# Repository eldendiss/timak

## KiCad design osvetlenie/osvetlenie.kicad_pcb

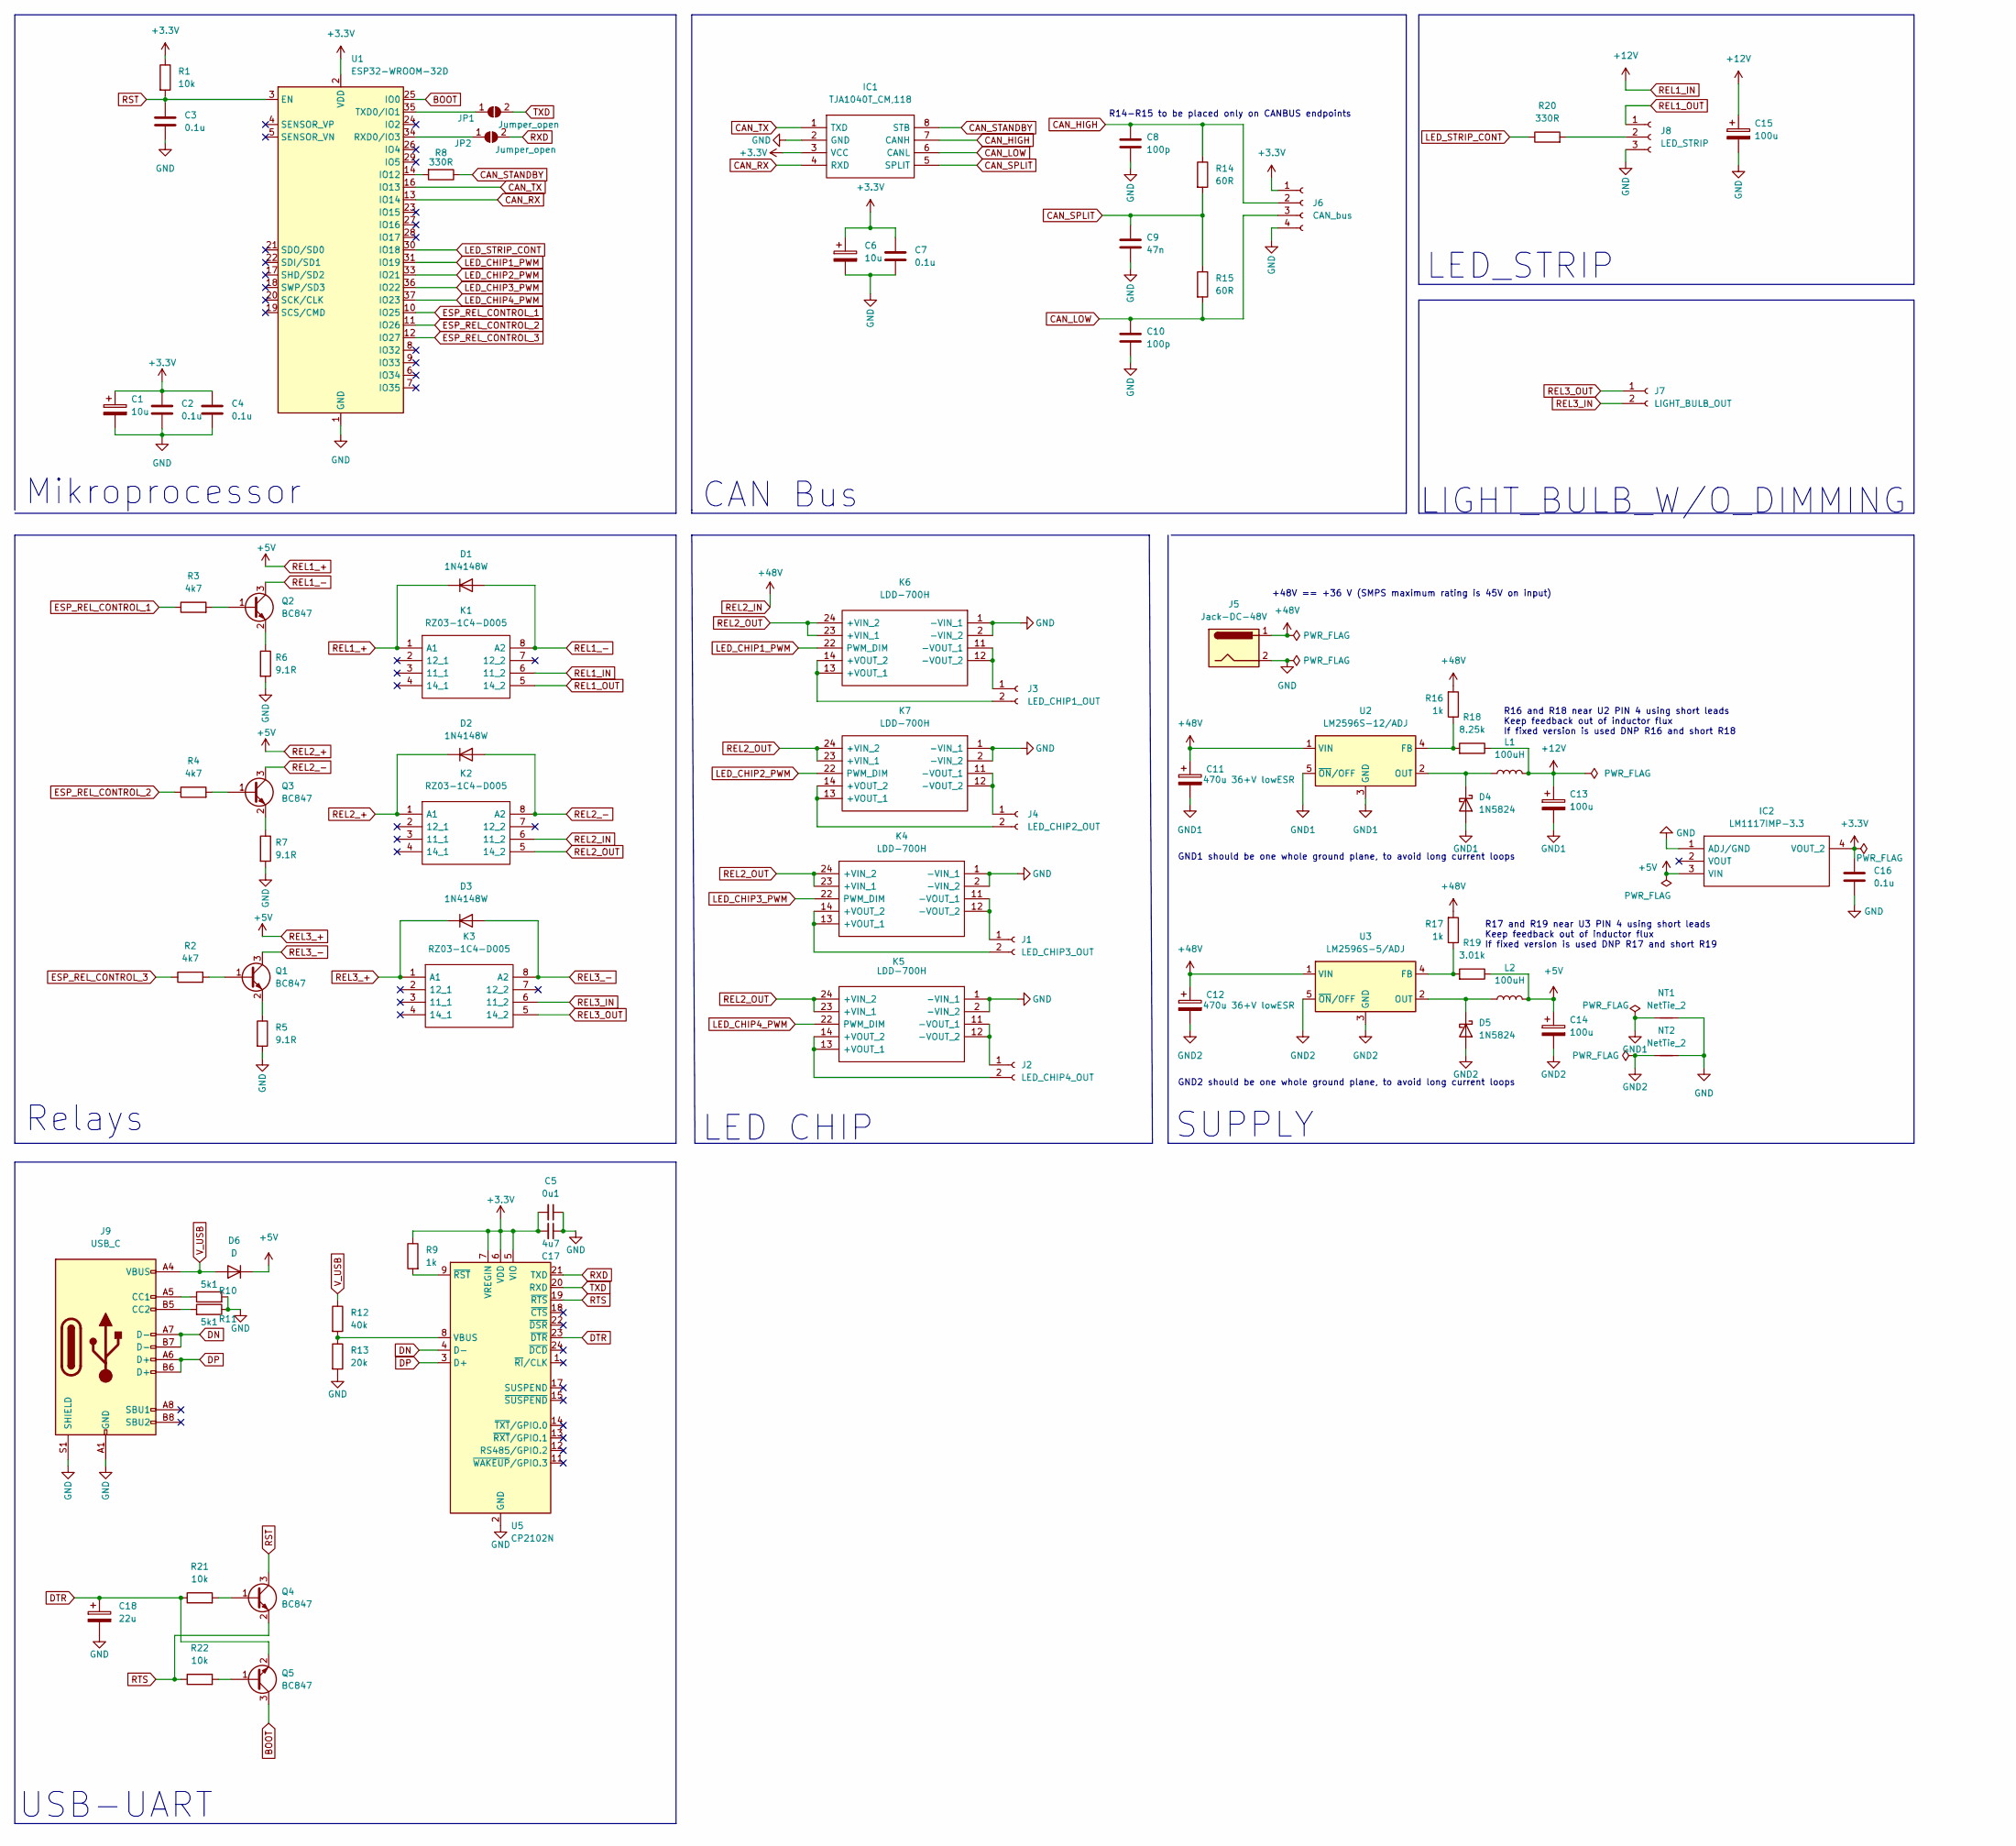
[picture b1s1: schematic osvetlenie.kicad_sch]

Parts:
C1, C6: 10u; C_0805_2012Metric
C2, C3, C4, C7, C16: 0.1u; C_0603_1608Metric
C5: 0u1; C_0603_1608Metric
C8, C10: 100p; C_0603_1608Metric
C9: 47n; C_0603_1608Metric
C11, C12: 470u 36+V lowESR; CP_Radial_D12.5mm_P5.00mm
C13, C14, C15: 100u; C_Elec_6.3x5.8
C17: 4u7; C_0603_1608Metric
C18: 22u; CP_EIA-3216-18_Kemet-A
D1, D2, D3: 1N4148W; D_SOD-123
D4, D5: 1N5824; D_SMA
D6: D; D_SOD-123
IC1: TJA1040T_CM,118; SOIC127P600X175-8N; Manufacturer_Part_Number TJA1040T/CM,118; Mouser Part Number 771-TJA1040T/CM118
IC2: LM1117IMP-3.3; SOT230P696X180-4N; Manufacturer_Part_Number LM1117IMP-3.3; Mouser Part Number 926-LM1117IMP-33
J1: LED_CHIP3_OUT; PhoenixContact_MSTBA_2,5_2-G_1x02_P5.00mm_Horizontal
J2: LED_CHIP4_OUT; PhoenixContact_MSTBA_2,5_2-G_1x02_P5.00mm_Horizontal
J3: LED_CHIP1_OUT; PhoenixContact_MSTBA_2,5_2-G_1x02_P5.00mm_Horizontal
J4: LED_CHIP2_OUT; PhoenixContact_MSTBA_2,5_2-G_1x02_P5.00mm_Horizontal
J5: Jack-DC-48V; PhoenixContact_MSTBA_2,5_2-G_1x02_P5.00mm_Horizontal
J6: CAN_bus; JST_PH_S4B-PH-K_1x04_P2.00mm_Horizontal
J7: LIGHT_BULB_OUT; PhoenixContact_MSTBA_2,5_2-G_1x02_P5.00mm_Horizontal
J8: LED_STRIP; JST_PH_S3B-PH-K_1x03_P2.00mm_Horizontal
J9: USB_C; USB_C_Receptacle_XKB_U262-16XN-4BVC11
JP1, JP2: Jumper_open; SolderJumper-2_P1.3mm_Open_RoundedPad1.0x1.5mm
K1, K2, K3: RZ03-1C4-D005; RZ03_1-FORM-C_; Manufacturer_Part_Number RZ03-1C4-D005; Mouser Part Number 655-RZ03-1C4-D005
K4, K5, K6, K7: LDD-700H; Manufacturer_Part_Number LDD-700H; Mouser Part Number 709-LDD-700H
L1, L2: 100uH; L_Bourns_SRP1770TA_16.9x16.9mm
NT1, NT2: NetTie_2; NetTie-2_SMD_Pad2.0mm
Q1, Q2, Q3, Q4, Q5: BC847; SOT-23
R1, R21, R22: 10k; R_0402_1005Metric
R2, R3, R4: 4k7; R_0402_1005Metric
R5, R6, R7: 9.1R; R_1206_3216Metric
R8, R20: 330R; R_0402_1005Metric
R9, R16, R17: 1k; R_0402_1005Metric
R10, R11: 5k1; R_0402_1005Metric
R12: 40k; R_0402_1005Metric
R13: 20k; R_0402_1005Metric
R14, R15: 60R; R_0402_1005Metric
R18: 8.25k; R_0402_1005Metric
R19: 3.01k; R_0402_1005Metric
U1: ESP32-WROOM-32D; ESP32-WROOM-32
U2: LM2596S-12/ADJ; TO-263-5_TabPin3
U3: LM2596S-5/ADJ; TO-263-5_TabPin3
U5: CP2102N; QFN-24-1EP_4x4mm_P0.5mm_EP2.6x2.6mm

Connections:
+3.3V: C1.1, C2.2, C4.1, C5.2, C6.1, C7.2, C16.2, C17.2, IC1.3 (VCC), IC2.4 (VOUT_2), J6.1, R1.1, R9.1, U1.2 (VDD), U5.5 (VIO), U5.6 (VDD), U5.7 (VREGIN)
BOOT: Q5.3 (C), U1.25 (IO0)
CAN_HIGH: C8.2, IC1.7 (CANH), J6.2, R14.1
CAN_LOW: C10.2, IC1.6 (CANL), J6.3, R15.2
CAN_RX: IC1.4 (RXD), U1.13 (IO14)
CAN_SPLIT: C9.2, IC1.5 (SPLIT), R14.2, R15.1
CAN_STANDBY: IC1.8 (STB), R8.1
CAN_TX: IC1.1 (TXD), U1.16 (IO13)
DN: J9.A7 (D-), J9.B7 (D-), U5.4 (D-)
DP: J9.A6 (D+), J9.B6 (D+), U5.3 (D+)
DTR: C18.1, Q5.2 (E), R21.1, U5.23 (~DTR)
ESP_REL_CONTROL_1: R3.1, U1.10 (IO25)
ESP_REL_CONTROL_2: R4.1, U1.11 (IO26)
ESP_REL_CONTROL_3: R2.1, U1.12 (IO27)
GND: C1.2, C2.1, C3.2, C4.2, C5.1, C6.2, C7.1, C8.1, C9.1, C10.1, C15.2, C16.1, C17.1, C18.2, IC1.2 (GND), IC2.1 (ADJ/GND), J5.2, J6.4, J8.3, J9.A1 (GND), J9.A12 (GND), J9.B1 (GND), J9.B12 (GND), J9.S1 (SHIELD), K4.1 (-VIN_1), K4.2 (-VIN_2), K5.1 (-VIN_1), K5.2 (-VIN_2), K6.1 (-VIN_1), K6.2 (-VIN_2), K7.1 (-VIN_1), K7.2 (-VIN_2), NT1.2, NT2.2, R5.2, R6.2, R7.2, R10.2, R11.1, R13.2, U1.1 (GND), U1.15 (GND), U1.38 (GND), U1.39 (GND), U5.2 (GND), U5.25 (GND)
GND1: C11.2, C13.2, D4.2 (A), NT1.1, U2.3 (GND), U2.5 (~ON/OFF)
GND2: C12.2, C14.2, D5.2 (A), NT2.1, U3.3 (GND), U3.5 (~ON/OFF)
LED_CHIP1_PWM: K6.22 (PWM_DIM), U1.31 (IO19)
LED_CHIP2_PWM: K7.22 (PWM_DIM), U1.33 (IO21)
LED_CHIP3_PWM: K4.22 (PWM_DIM), U1.36 (IO22)
LED_CHIP4_PWM: K5.22 (PWM_DIM), U1.37 (IO23)
LED_STRIP_CONT: R20.1, U1.30 (IO18)
unnamed: D4.1 (K), L1.1, U2.2 (OUT)
unnamed: D5.1 (K), L2.1, U3.2 (OUT)
unnamed: J1.1, K4.11 (-VOUT_1), K4.12 (-VOUT_2)
unnamed: J1.2, K4.13 (+VOUT_1), K4.14 (+VOUT_2)
unnamed: J2.1, K5.11 (-VOUT_1), K5.12 (-VOUT_2)
unnamed: J2.2, K5.13 (+VOUT_1), K5.14 (+VOUT_2)
unnamed: J3.1, K6.11 (-VOUT_1), K6.12 (-VOUT_2)
unnamed: J3.2, K6.13 (+VOUT_1), K6.14 (+VOUT_2)
unnamed: J4.1, K7.11 (-VOUT_1), K7.12 (-VOUT_2)
unnamed: J4.2, K7.13 (+VOUT_1), K7.14 (+VOUT_2)
unnamed: J8.2, R20.2
unnamed: J9.A5 (CC1), R10.1
unnamed: J9.B5 (CC2), R11.2
unnamed: JP1.1 (A), U1.35 (TXD0/IO1)
unnamed: JP2.1 (A), U1.34 (RXD0/IO3)
unnamed: Q1.1 (B), R2.2
unnamed: Q1.2 (E), R5.1
unnamed: Q2.1 (B), R3.2
unnamed: Q2.2 (E), R6.1
unnamed: Q3.1 (B), R4.2
unnamed: Q3.2 (E), R7.1
unnamed: Q4.1 (B), R21.2
unnamed: Q5.1 (B), R22.2
unnamed: R8.2, U1.14 (IO12)
unnamed: R9.2, U5.9 (~RST)
unnamed: R12.2, R13.1, U5.8 (VBUS)
unnamed: R16.1, R18.2, U2.4 (FB)
unnamed: R17.1, R19.2, U3.4 (FB)
REL1_+: C14.1, D1.1 (K), D2.1 (K), D3.1 (K), D6.1 (K), IC2.3 (VIN), K1.1 (A1), K2.1 (A1), K3.1 (A1), L2.2, R19.1
REL1_-: D1.2 (A), K1.8 (A2), Q2.3 (C)
REL1_IN: C13.1, C15.1, K1.6 (11_2), L1.2, R18.1
REL1_OUT: J8.1, K1.5 (14_2)
REL2_-: D2.2 (A), K2.8 (A2), Q3.3 (C)
REL2_IN: C11.1, C12.1, J5.1, K2.6 (11_2), R16.2, R17.2, U2.1 (VIN), U3.1 (VIN)
REL2_OUT: K2.5 (14_2), K4.23 (+VIN_1), K4.24 (+VIN_2), K5.23 (+VIN_1), K5.24 (+VIN_2), K6.23 (+VIN_1), K6.24 (+VIN_2), K7.23 (+VIN_1), K7.24 (+VIN_2)
REL3_-: D3.2 (A), K3.8 (A2), Q1.3 (C)
REL3_IN: J7.2, K3.6 (11_2)
REL3_OUT: J7.1, K3.5 (14_2)
RST: C3.1, Q4.3 (C), R1.2, U1.3 (EN)
RTS: Q4.2 (E), R22.1, U5.19 (~RTS)
RXD: JP2.2 (B), U5.21 (TXD)
TXD: JP1.2 (B), U5.20 (RXD)
V_USB: D6.2 (A), J9.A4 (VBUS), J9.A9 (VBUS), J9.B4 (VBUS), J9.B9 (VBUS), R12.1

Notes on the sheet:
GND2 should be one whole ground plane, to avoid long current loops
Relays
CAN Bus
SUPPLY
R17 and R19 near U3 PIN 4 using short leads Keep feedback out of inductor flux If fixed version is used DNP R17 and short R19
LIGHT_BULB_W/O_DIMMING
LED CHIP
USB-UART
R14-R15 to be placed only on CANBUS endpoints
GND1 should be one whole ground plane, to avoid long current loops
Mikroprocessor
R16 and R18 near U2 PIN 4 using short leads Keep feedback out of inductor flux If fixed version is used DNP R16 and short R18
+48V == +36 V (SMPS maximum rating is 45V on input)
LED_STRIP

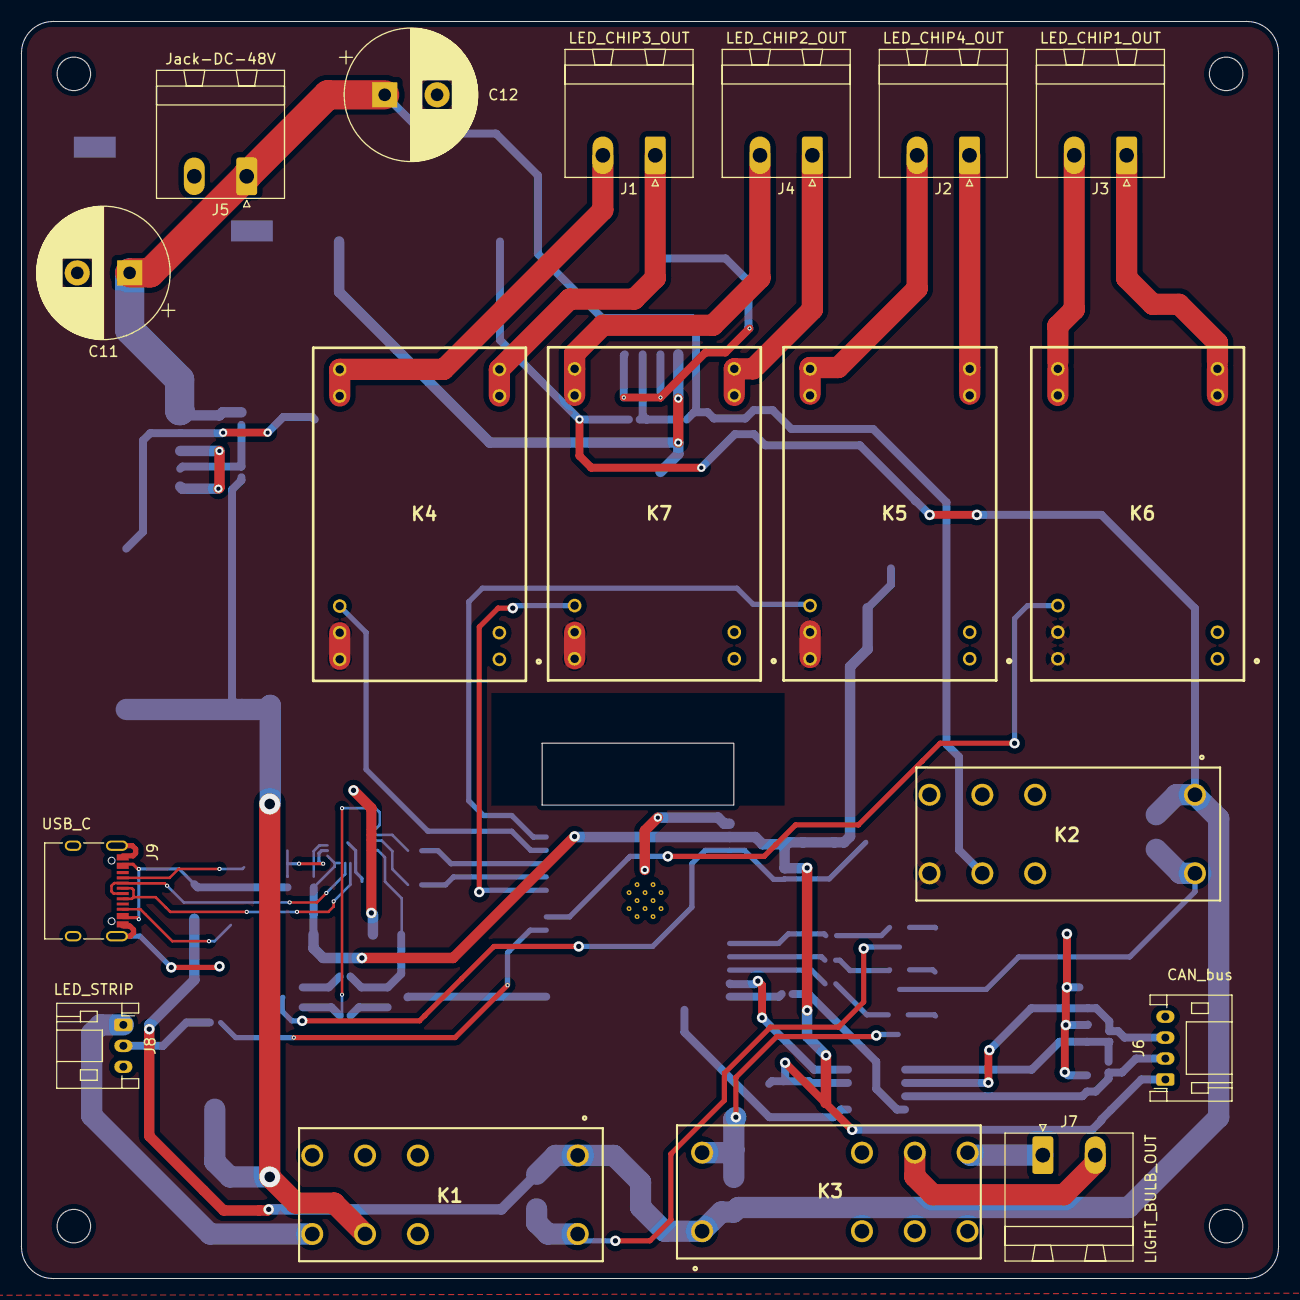
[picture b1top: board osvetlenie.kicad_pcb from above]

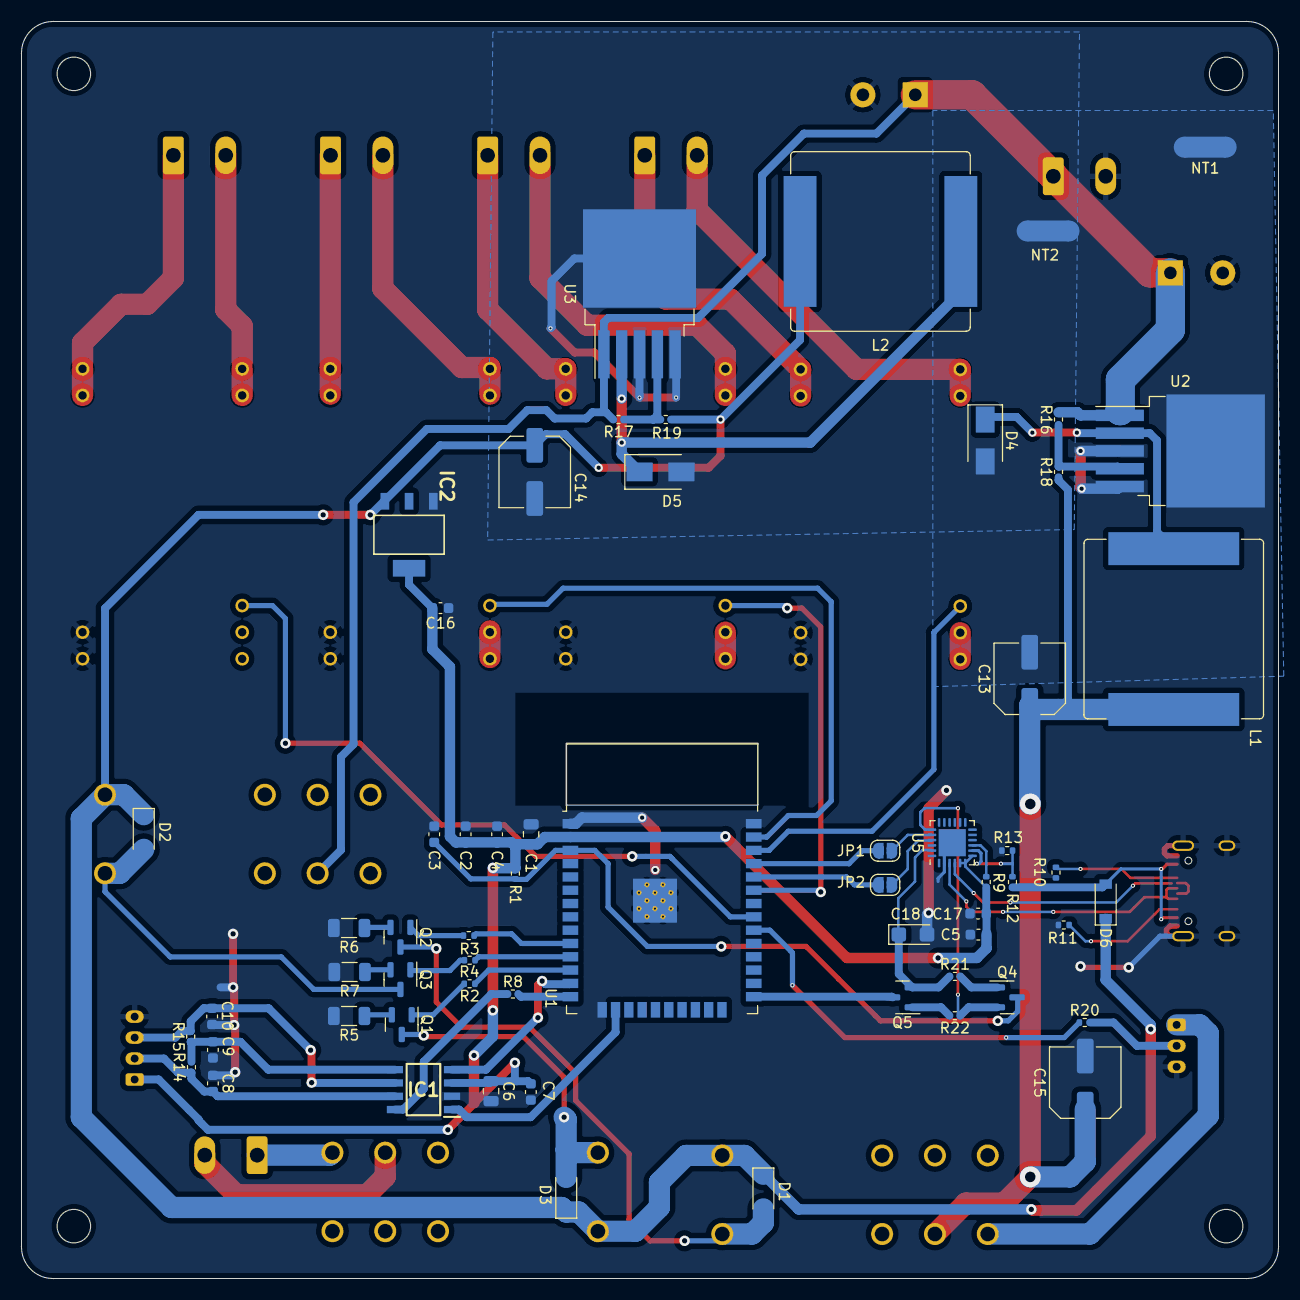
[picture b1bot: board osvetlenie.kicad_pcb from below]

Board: 2 copper layers, 120.0 x 120.0 mm, 79 parts (61 on the bottom side), 65 nets.

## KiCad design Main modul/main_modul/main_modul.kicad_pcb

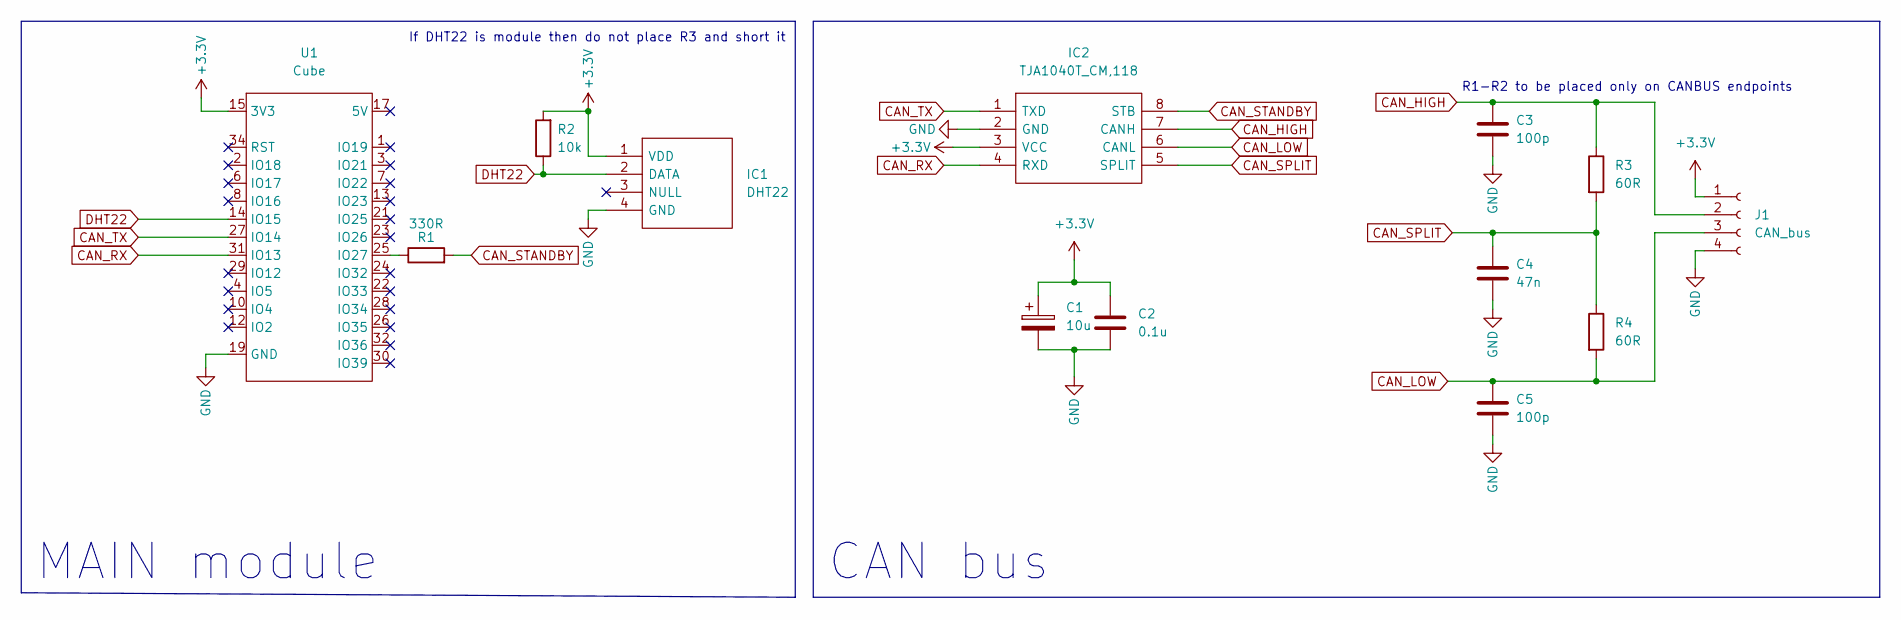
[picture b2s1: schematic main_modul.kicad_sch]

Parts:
C1: 10u; C_0805_2012Metric
C2: 0.1u; C_0603_1608Metric
C3, C5: 100p; C_0603_1608Metric
C4: 47n; C_0603_1608Metric
IC1: DHT22; Manufacturer_Part_Number DHT22
IC2: TJA1040T_CM,118; SOIC127P600X175-8N; Manufacturer_Part_Number TJA1040T/CM,118; Mouser Part Number 771-TJA1040T/CM118
J1: CAN_bus; JST_PH_S4B-PH-K_1x04_P2.00mm_Horizontal
R1: 330R; R_0402_1005Metric
R2: 10k; R_0402_1005Metric
R3, R4: 60R; R_0402_1005Metric
U1: Cube; THT 20x2x2

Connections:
+3.3V: C1.1, C2.2, IC1.1 (VDD), IC2.3 (VCC), J1.1, R2.2, U1.15 (3V3)
CAN_HIGH: C3.2, IC2.7 (CANH), J1.2, R3.1
CAN_LOW: C5.2, IC2.6 (CANL), J1.3, R4.2
CAN_RX: IC2.4 (RXD), U1.31 (IO13)
CAN_SPLIT: C4.2, IC2.5 (SPLIT), R3.2, R4.1
CAN_STANDBY: IC2.8 (STB), R1.2
CAN_TX: IC2.1 (TXD), U1.27 (IO14)
DHT22: IC1.2 (DATA), R2.1, U1.14 (IO15)
GND: C1.2, C2.1, C3.1, C4.1, C5.1, IC1.4 (GND), IC2.2 (GND), J1.4, U1.19 (GND)
unnamed: R1.1, U1.25 (IO27)

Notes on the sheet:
R1-R2 to be placed only on CANBUS endpoints
If DHT22 is module then do not place R3 and short it
CAN bus
MAIN module

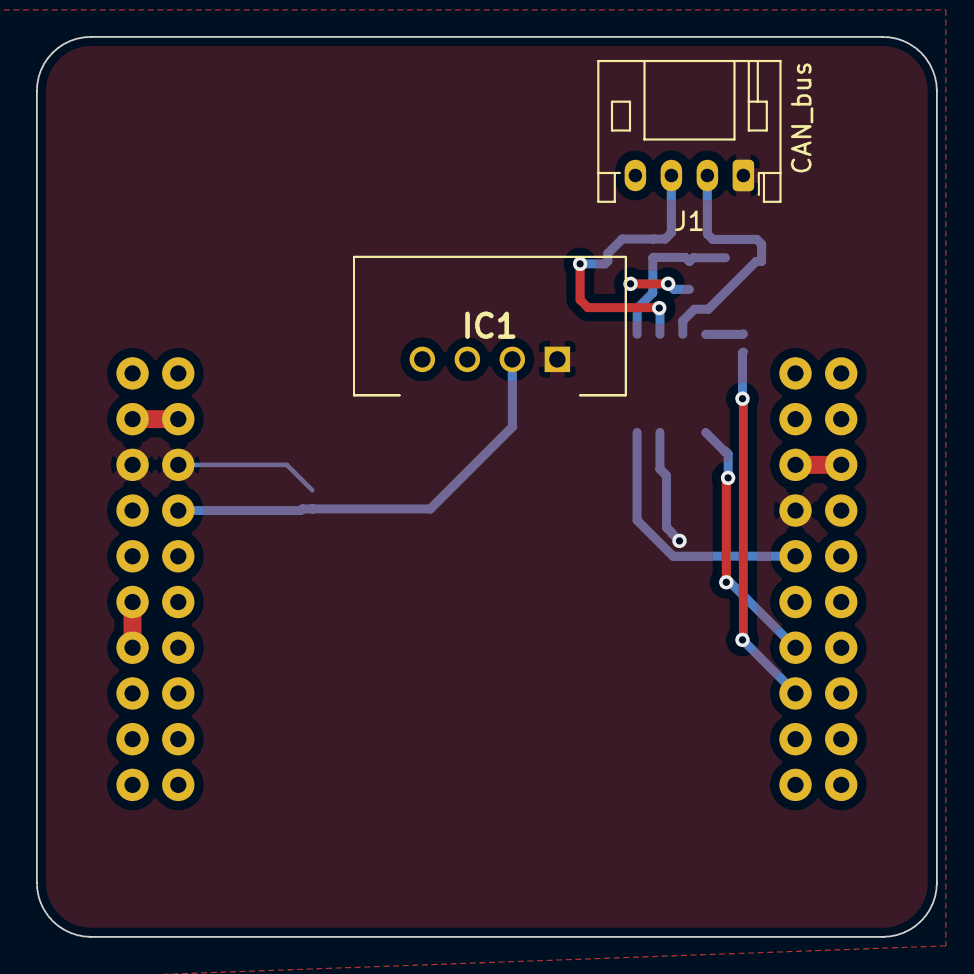
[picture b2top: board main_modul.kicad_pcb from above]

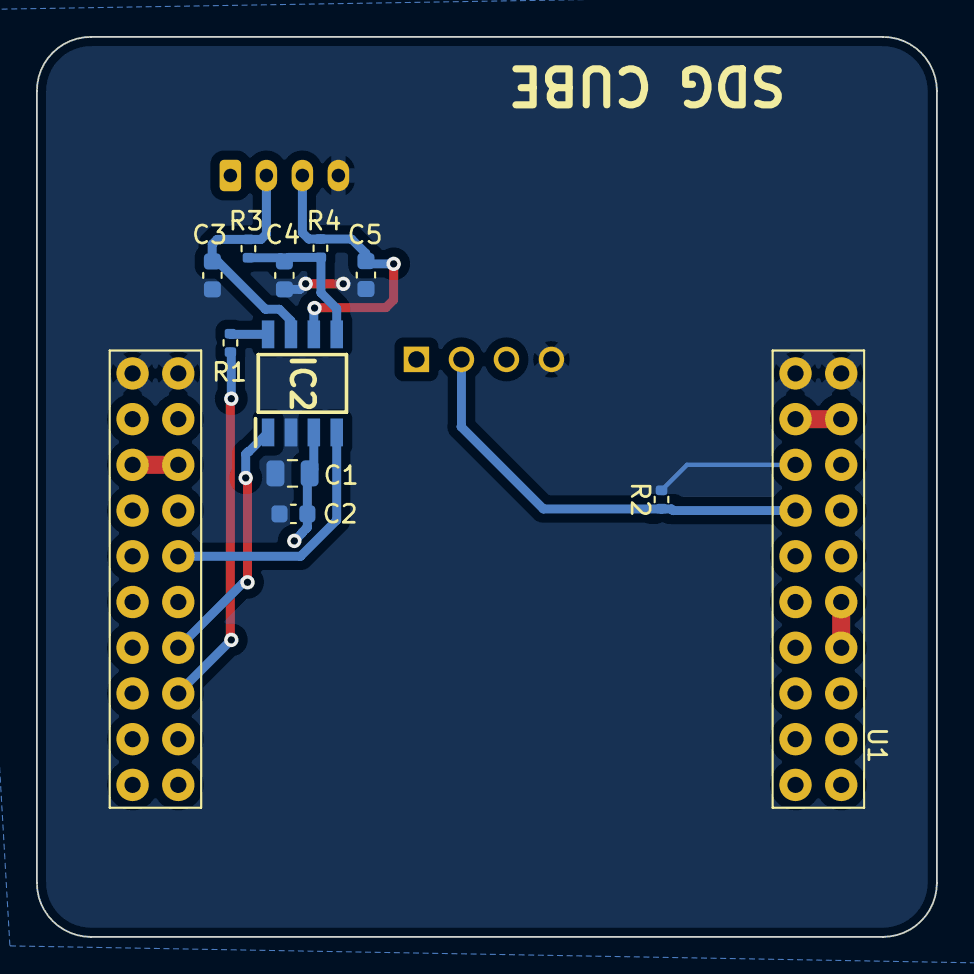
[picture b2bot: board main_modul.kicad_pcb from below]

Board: 2 copper layers, 50.0 x 50.0 mm, 13 parts (10 on the bottom side), 10 nets.

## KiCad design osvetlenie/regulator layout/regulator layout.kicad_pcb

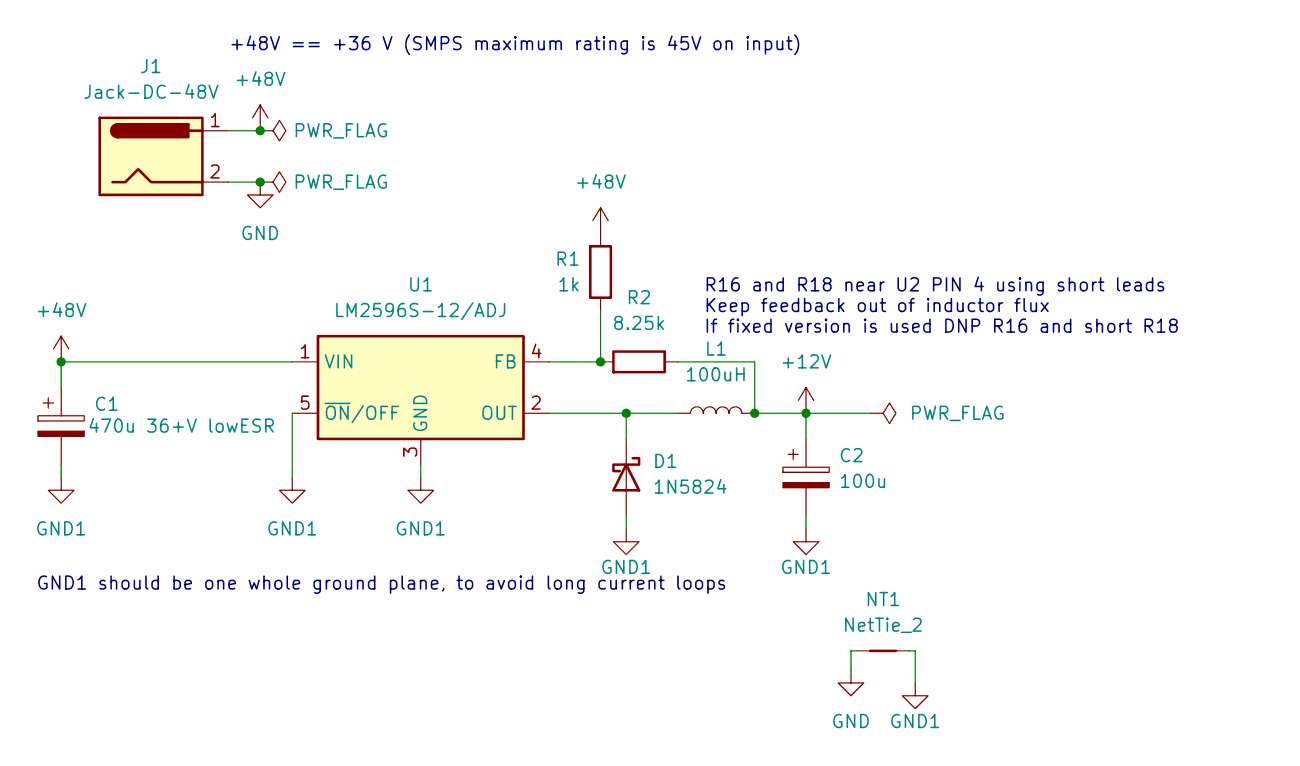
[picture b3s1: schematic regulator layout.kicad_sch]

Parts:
C1: 470u 36+V lowESR; CP_Radial_D12.5mm_P5.00mm
C2: 100u; C_Elec_6.3x5.8
D1: 1N5824; D_SMA
J1: Jack-DC-48V; PhoenixContact_MSTBA_2,5_2-G_1x02_P5.00mm_Horizontal
L1: 100uH; L_Bourns_SRP1770TA_16.9x16.9mm
NT1: NetTie_2; NetTie-2_SMD_Pad2.0mm
R1: 1k; R_0402_1005Metric
R2: 8.25k; R_0402_1005Metric
U1: LM2596S-12/ADJ; TO-263-5_TabPin3

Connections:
+12V: C2.1, L1.2, R2.1
+48V: C1.1, J1.1, R1.2, U1.1 (VIN)
GND: J1.2, NT1.1
GND1: C1.2, C2.2, D1.2 (A), NT1.2, U1.3 (GND), U1.5 (~ON/OFF)
unnamed: D1.1 (K), L1.1, U1.2 (OUT)
unnamed: R1.1, R2.2, U1.4 (FB)

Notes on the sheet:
+48V == +36 V (SMPS maximum rating is 45V on input)
R16 and R18 near U2 PIN 4 using short leads Keep feedback out of inductor flux If fixed version is used DNP R16 and short R18
GND1 should be one whole ground plane, to avoid long current loops

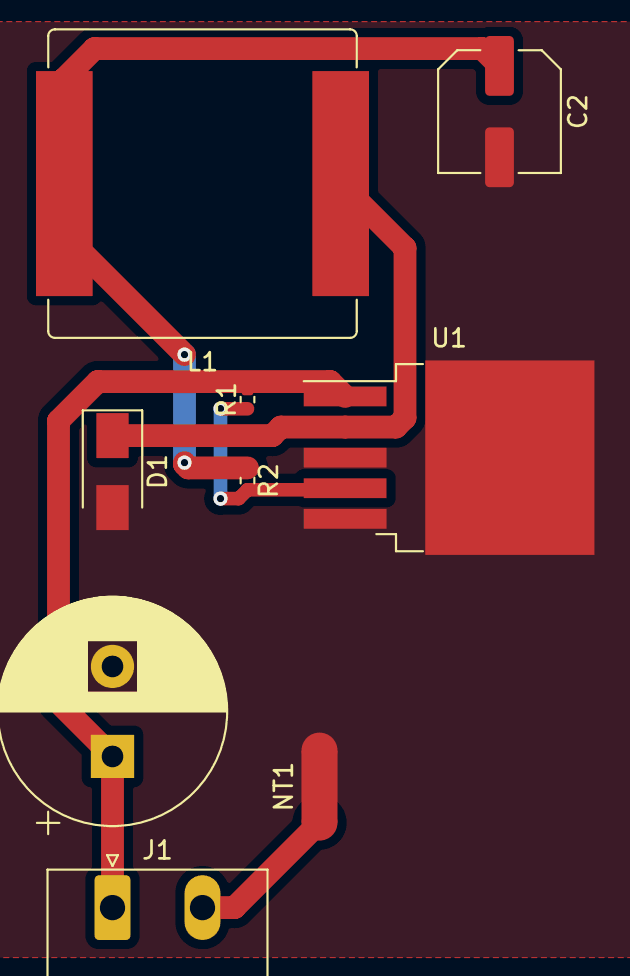
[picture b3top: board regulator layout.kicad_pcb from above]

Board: 2 copper layers, 9 parts (0 on the bottom side), 6 nets.

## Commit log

2022-10-16 Added PSU and footprints
2022-10-23 Added PCB
2022-10-31 added main module
